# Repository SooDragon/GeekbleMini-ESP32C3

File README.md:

GeekbleMini-ESP32C3
=============
GeekbleMini-ESP32C3 문서에 오신것을 환영합니다

아두이노 IDE에서 쉽게 사용할 수 있는 Geekble Mini를 통해 WiFi, Bluetooth 기능을 여러분의 프로젝트에 구현할 수 있습니다

Geekble Mini 핀맵
-------------

GeekbleMini PinMap

Geekble Mini 회로도
-------------

GeekbleMini Schematic

Geekble Mini 치수도
-------------

GeekbleMini Dimension

Geekble Mini KiCad 라이브러리 by [@Alcyone-0022](https://github.com/Alcyone-0022)
-------------

KiCad 프로젝트에 사용 가능한 Footprint가 존재합니다.    
**Geekble Mini ESP32C3FH4.pretty** 폴더와 **Geekble Mini ESP32C3FH4.kicad_sym** 파일을 KiCad 프로젝트 폴더에 옮긴 뒤,    
각각 풋프린트 에디터→파일→라이브러리 추가→프로젝트 선택→확인→**Geekble Mini ESP32C3FH4.pretty** 폴더 선택,    
심볼 에디터→파일→라이브러리 추가→프로젝트 선택→확인→**Geekble Mini ESP32C3FH4.kicad_sym** 파일 선택하여 추가하신 뒤 사용해 주세요.

Geekble Mini Version Log
-------------
- Ver.1.0.0: 최초 공개 버전
- Ver.1.1.0: Vin/VUSB 설계 변경, VUSB에서 Vin 방향으로 전류가 흐르지 않도록 회로 및 아트웍 수정, Vin에 배터리가 연결 된 상태에서 USB를 연결할 수 있다
- Ver.1.1.1: 핀헤더에 의해 실크가 가려지지 않게 배치 수정
- Ver.2.0: A5(ADC1)핀 D5핀으로 재배치, 재배치에 따른 핀 위치 수정

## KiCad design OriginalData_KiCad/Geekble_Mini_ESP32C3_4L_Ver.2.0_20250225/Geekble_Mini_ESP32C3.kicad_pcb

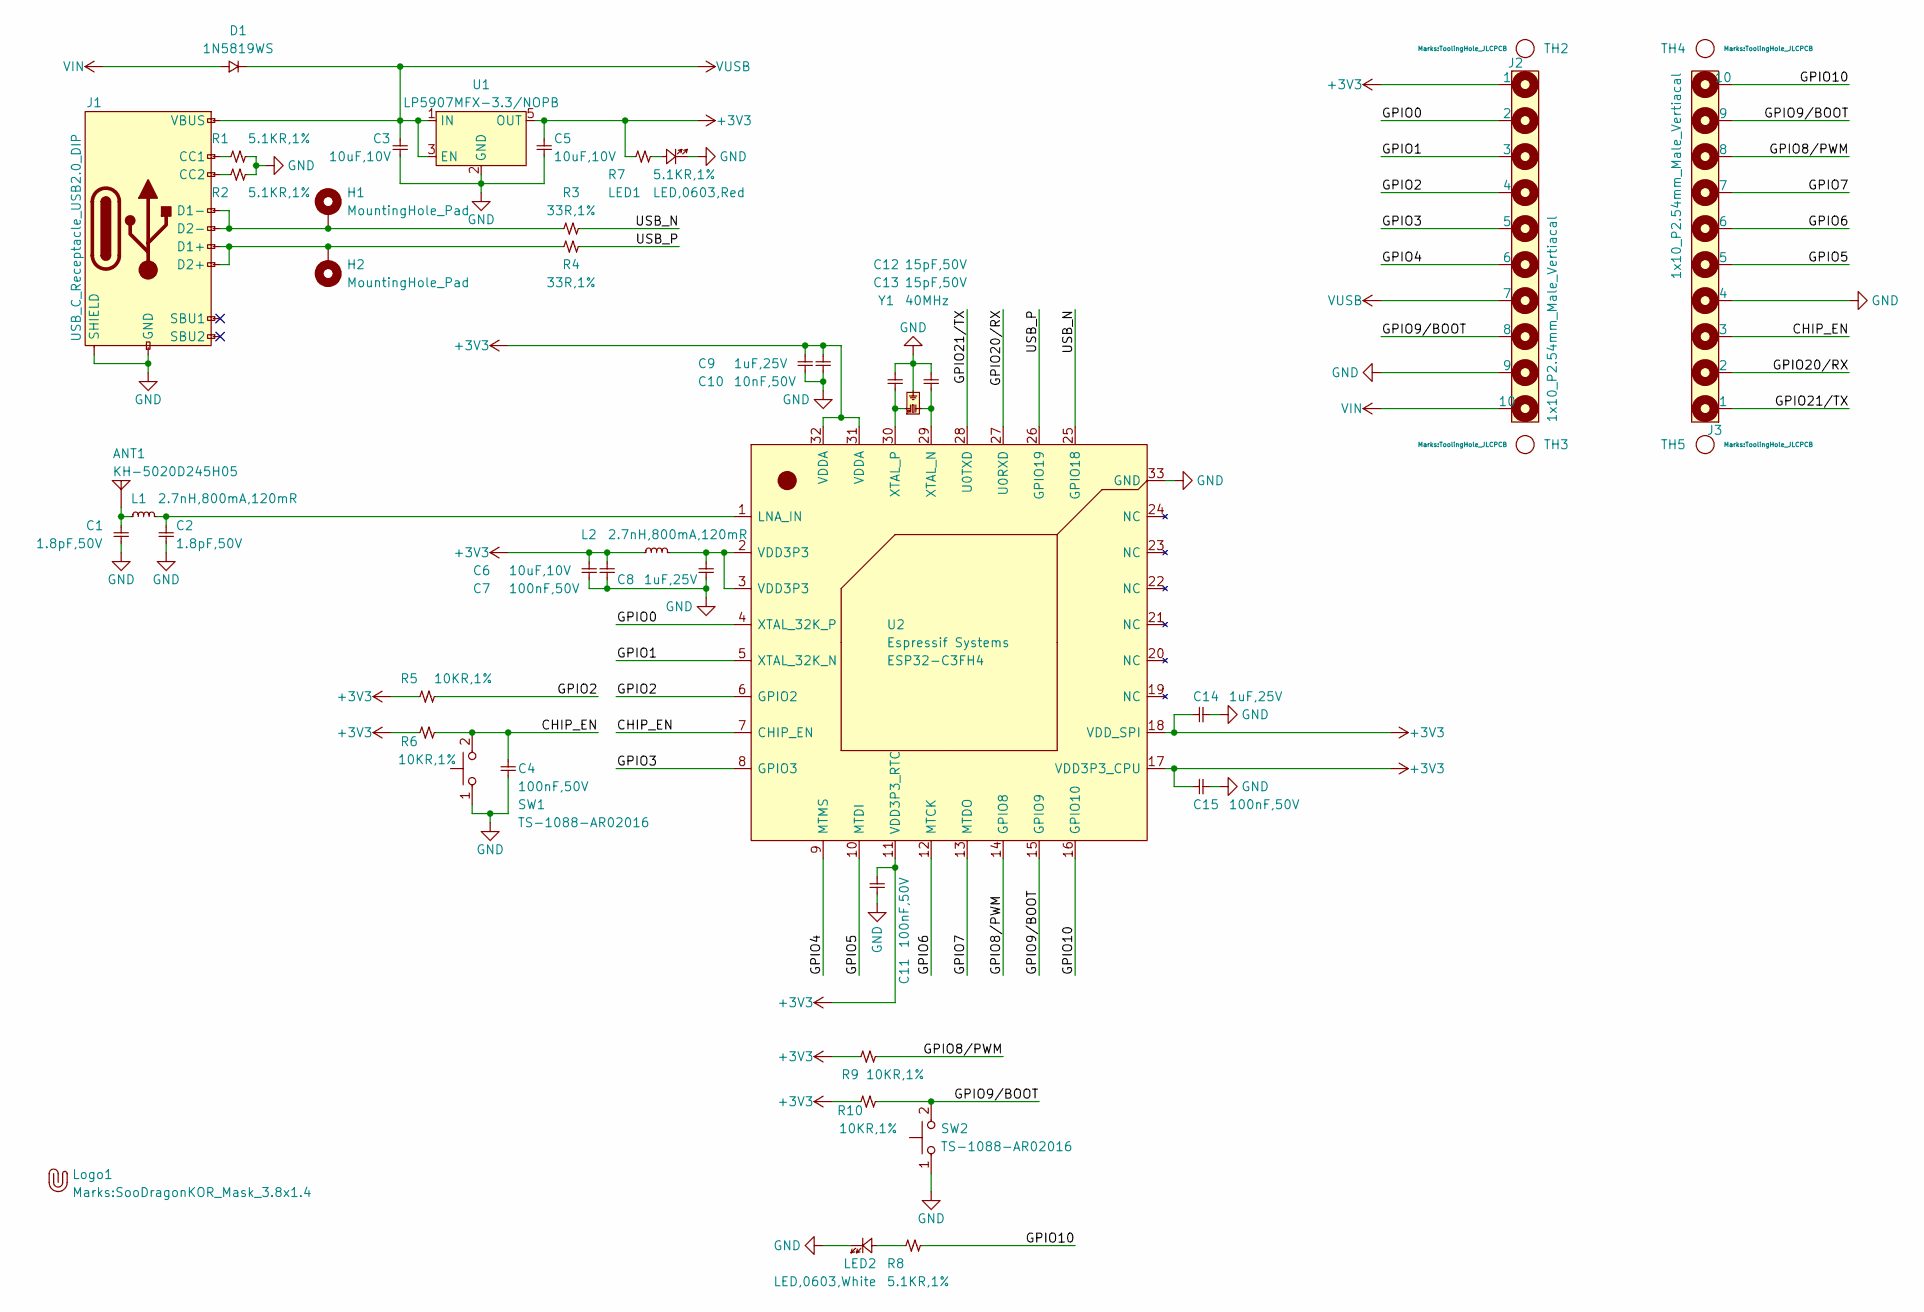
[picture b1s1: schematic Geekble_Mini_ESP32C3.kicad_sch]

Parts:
ANT1: KH-5020D245H05; ANT_5020; Manufacturer Part Number KH-5020D245H05; LCSC C45359218
C1, C2: 1.8pF,50V; C_0402; Manufacturer Part Number CC0402BRNPO9BN1R8; LCSC C327209
C3, C5, C6: 10uF,10V; C_0402; Manufacturer Part Number LDK105CBJ106MVLF; LCSC C386033
C4, C7, C11, C15: 100nF,50V; C_0402; Manufacturer Part Number CL05B104KB54PNC; LCSC C307331
C8, C9, C14: 1uF,25V; C_0402; Manufacturer Part Number CL05A105KA5NQNC; LCSC C52923
C10: 10nF,50V; C_0402; Manufacturer Part Number CL05B103KB5NNNC; LCSC C15195
C12, C13: 15pF,50V; C_0402; Manufacturer Part Number 0402CG150J500NT; LCSC C1548
D1: 1N5819WS; SOD-323F; Manufacturer Part Number 1N5819WS; LCSC C191023
H1, H2: MountingHole_Pad; 1x1_1.0piPad_SMD
J1: USB_C_Receptacle_USB2.0_DIP; USB_DIP,8.94x7.3mm; Manufacturer Part Number TYPE-C-31-M-12; LCSC C165948
J2, J3: 1x10_P2.54mm_Male_Vertiacal; 1x10_P2.54_CastellatedPad_PinHeader; Manufacturer Part Number 2541WV-10P; LCSC C5383117
L1, L2: 2.7nH,800mA,120mR; L_0402; Manufacturer Part Number LQG15HS2N7S02D; LCSC C77108
LED1: LED,0603,Red; LED_0603_Red; Manufacturer Part Number KT-0603R; LCSC C2286
LED2: LED,0603,White; LED_0603_White; LCSC C2290
Logo1: Geekble_Logo; SooDragonKOR_Mask_3.8x1.4
R1, R2, R7, R8: 5.1KR,1%; R_0402; Manufacturer Part Number 0402WGF5101TCE; LCSC C25905
R3, R4: 33R,1%; R_0402; Manufacturer Part Number 0402WGF330JTCE; LCSC C25105
R5, R6, R9, R10: 10KR,1%; R_0402; Manufacturer Part Number 0402WGF1002TCE; LCSC C25744
SW1, SW2: TS-1088-AR02016; TS-1088-AR020; Manufacturer Part Number TS-1088-AR02016; LCSC C720477
TH2, TH3, TH4, TH5: ToolingHole; ToolingHole_JLCPCB
U1: LP5907MFX-3.3/NOPB; SOT-23-5; Manufacturer Part Number LP5907MFX-3.3/NOPB; LCSC C80670
U2: ESP32-C3FH4; QFN-32-EP(5x5); Manufacturer Part Number ESP32-C3FH4; LCSC C2858491
Y1: 40MHz; SMD-3225_4P; Manufacturer Part Number X322540MPB4SI; LCSC C9010

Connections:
+3V3: C5.2, C6.2, C7.2, C9.2, C10.2, C11.2, C14.2, C15.2, J2.1, L2.1, R5.1, R6.1, R7.1, R9.1, R10.1, U1.5 (OUT), U2.11 (VDD3P3_RTC), U2.17 (VDD3P3_CPU), U2.18 (VDD_SPI), U2.31 (VDDA), U2.32 (VDDA)
/CHIP_EN: C4.2, J3.3, R6.2, SW1.2 (B), U2.7 (CHIP_EN)
/GPIO0: J2.2, U2.4 (XTAL_32K_P)
/GPIO1: J2.3, U2.5 (XTAL_32K_N)
/GPIO2: J2.4, R5.2, U2.6 (GPIO2)
/GPIO3: J2.5, U2.8 (GPIO3)
/GPIO4: J2.6, U2.9 (MTMS)
/GPIO5: J3.5, U2.10 (MTDI)
/GPIO6: J3.6, U2.12 (MTCK)
/GPIO7: J3.7, U2.13 (MTDO)
/GPIO8/PWM: J3.8, R9.2, U2.14 (GPIO8)
/GPIO9/BOOT: J2.8, J3.9, R10.2, SW2.2 (B), U2.15 (GPIO9)
/GPIO10: J3.10, R8.2, U2.16 (GPIO10)
/GPIO20/RX: J3.2, U2.27 (U0RXD)
/GPIO21/TX: J3.1, U2.28 (U0TXD)
/USB_N: R3.2, U2.25 (GPIO18)
/USB_P: R4.2, U2.26 (GPIO19)
GND: C1.1, C2.1, C3.1, C4.1, C5.1, C6.1, C7.1, C8.1, C9.1, C10.1, C11.1, C12.1, C13.1, C14.1, C15.1, J1.A1B12 (GND), J1.B1A12 (GND), J1.S1 (SHIELD), J1.S2 (SHIELD), J1.S3 (SHIELD), J1.S4 (SHIELD), J2.9, J3.4, LED1.C, LED2.C, R1.2, R2.2, SW1.1 (A), SW2.1 (A), U1.2 (GND), U2.33 (GND), Y1.2 (GND), Y1.4 (GND)
unnamed: ANT1.Feed, C1.2, L1.1
unnamed: C8.2, L2.2, U2.2 (VDD3P3), U2.3 (VDD3P3)
unnamed: J1.A5 (CC1), R1.1
unnamed: J1.B5 (CC2), R2.1
unnamed: H2.1, J1.A6 (D1+), J1.B6 (D2+), R4.1
unnamed: H1.1, J1.A7 (D1-), J1.B7 (D2-), R3.1
unnamed: LED1.A, R7.2
unnamed: LED2.A, R8.1
unnamed: C2.2, L1.2, U2.1 (LNA_IN)
unnamed: C13.2, U2.29 (XTAL_N), Y1.3 (OSC2)
unnamed: C12.2, U2.30 (XTAL_P), Y1.1 (OSC1)
VIN: D1.A, J2.10
VUSB: C3.2, D1.C, J1.A4B9 (VBUS), J1.B4A9 (VBUS), J2.7, U1.1 (IN), U1.3 (EN)

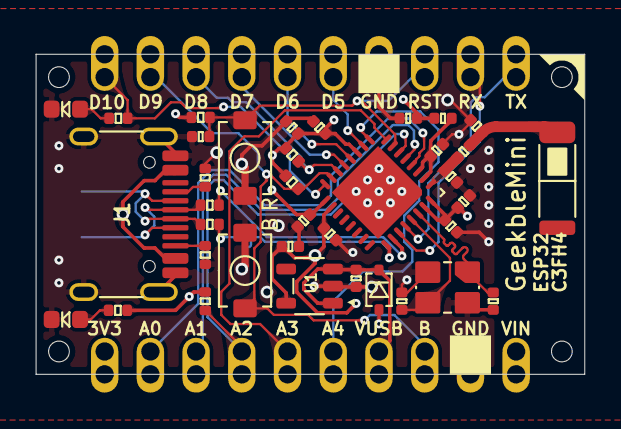
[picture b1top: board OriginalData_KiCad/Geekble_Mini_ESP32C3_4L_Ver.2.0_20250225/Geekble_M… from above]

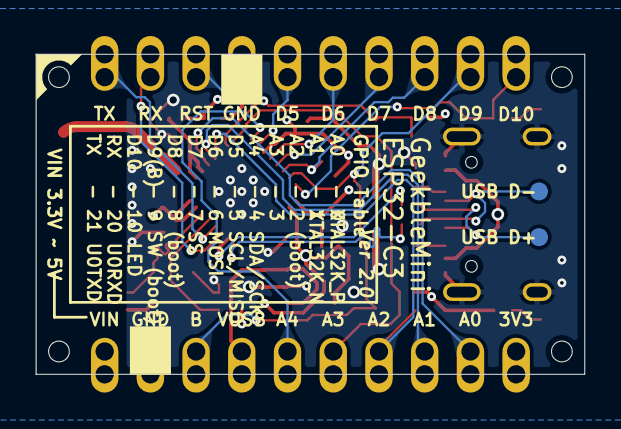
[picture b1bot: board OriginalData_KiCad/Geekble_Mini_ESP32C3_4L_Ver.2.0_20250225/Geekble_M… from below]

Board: 4 copper layers, 30.5 x 17.8 mm, 46 parts (4 on the bottom side), 31 nets.

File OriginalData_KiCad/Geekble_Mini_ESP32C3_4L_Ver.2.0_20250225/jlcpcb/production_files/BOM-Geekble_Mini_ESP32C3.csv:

Comment,Designator,Footprint,LCSC,Quantity
"10nF,50V",C10,C_0402,C15195,1
"15pF,50V","C12,C13",C_0402,C1548,2
USB_C_Receptacle_USB2.0_DIP,J1,"USB_DIP,8.94x7.3mm",C165948,1
1N5819WS,D1,SOD-323F,C191023,1
"LED,0603,Red",LED1,LED_0603_Red,C2286,1
"LED,0603,White",LED2,LED_0603_White,C2290,1
"33R,1%","R3,R4",R_0402,C25105,2
"10KR,1%","R10,R5,R6,R9",R_0402,C25744,4
"5.1KR,1%","R1,R2,R7,R8",R_0402,C25905,4
ESP32-C3FH4,U2,QFN-32-EP(5x5),C2858491,1
"100nF,50V","C11,C15,C4,C7",C_0402,C307331,4
"1.8pF,50V","C1,C2",C_0402,C327209,2
"10uF,10V","C3,C5,C6",C_0402,C386033,3
KH-5020D245H05,ANT1,ANT_5020,C45359218,1
"1uF,25V","C14,C8,C9",C_0402,C52923,3
1x10_P2.54mm_Male_Vertiacal,"J2,J3",1x10_P2.54_CastellatedPad_PinHeader,C5383117,2
TS-1088-AR02016,"SW1,SW2",TS-1088-AR020,C720477,2
"2.7nH,800mA,120mR","L1,L2",L_0402,C77108,2
LP5907MFX-3.3/NOPB,U1,SOT-23-5,C80670,1
40MHz,Y1,SMD-3225_4P,C9010,1
ToolingHole,TH4,ToolingHole_JLCPCB,,1
ToolingHole,TH5,ToolingHole_JLCPCB,,1
Geekble_Logo,Logo1,SooDragonKOR_Mask_3.8x1.4,,1
ToolingHole,TH3,ToolingHole_JLCPCB,,1
ToolingHole,TH2,ToolingHole_JLCPCB,,1
MountingHole_Pad,H2,1x1_1.0piPad_SMD,,1
MountingHole_Pad,H1,1x1_1.0piPad_SMD,,1

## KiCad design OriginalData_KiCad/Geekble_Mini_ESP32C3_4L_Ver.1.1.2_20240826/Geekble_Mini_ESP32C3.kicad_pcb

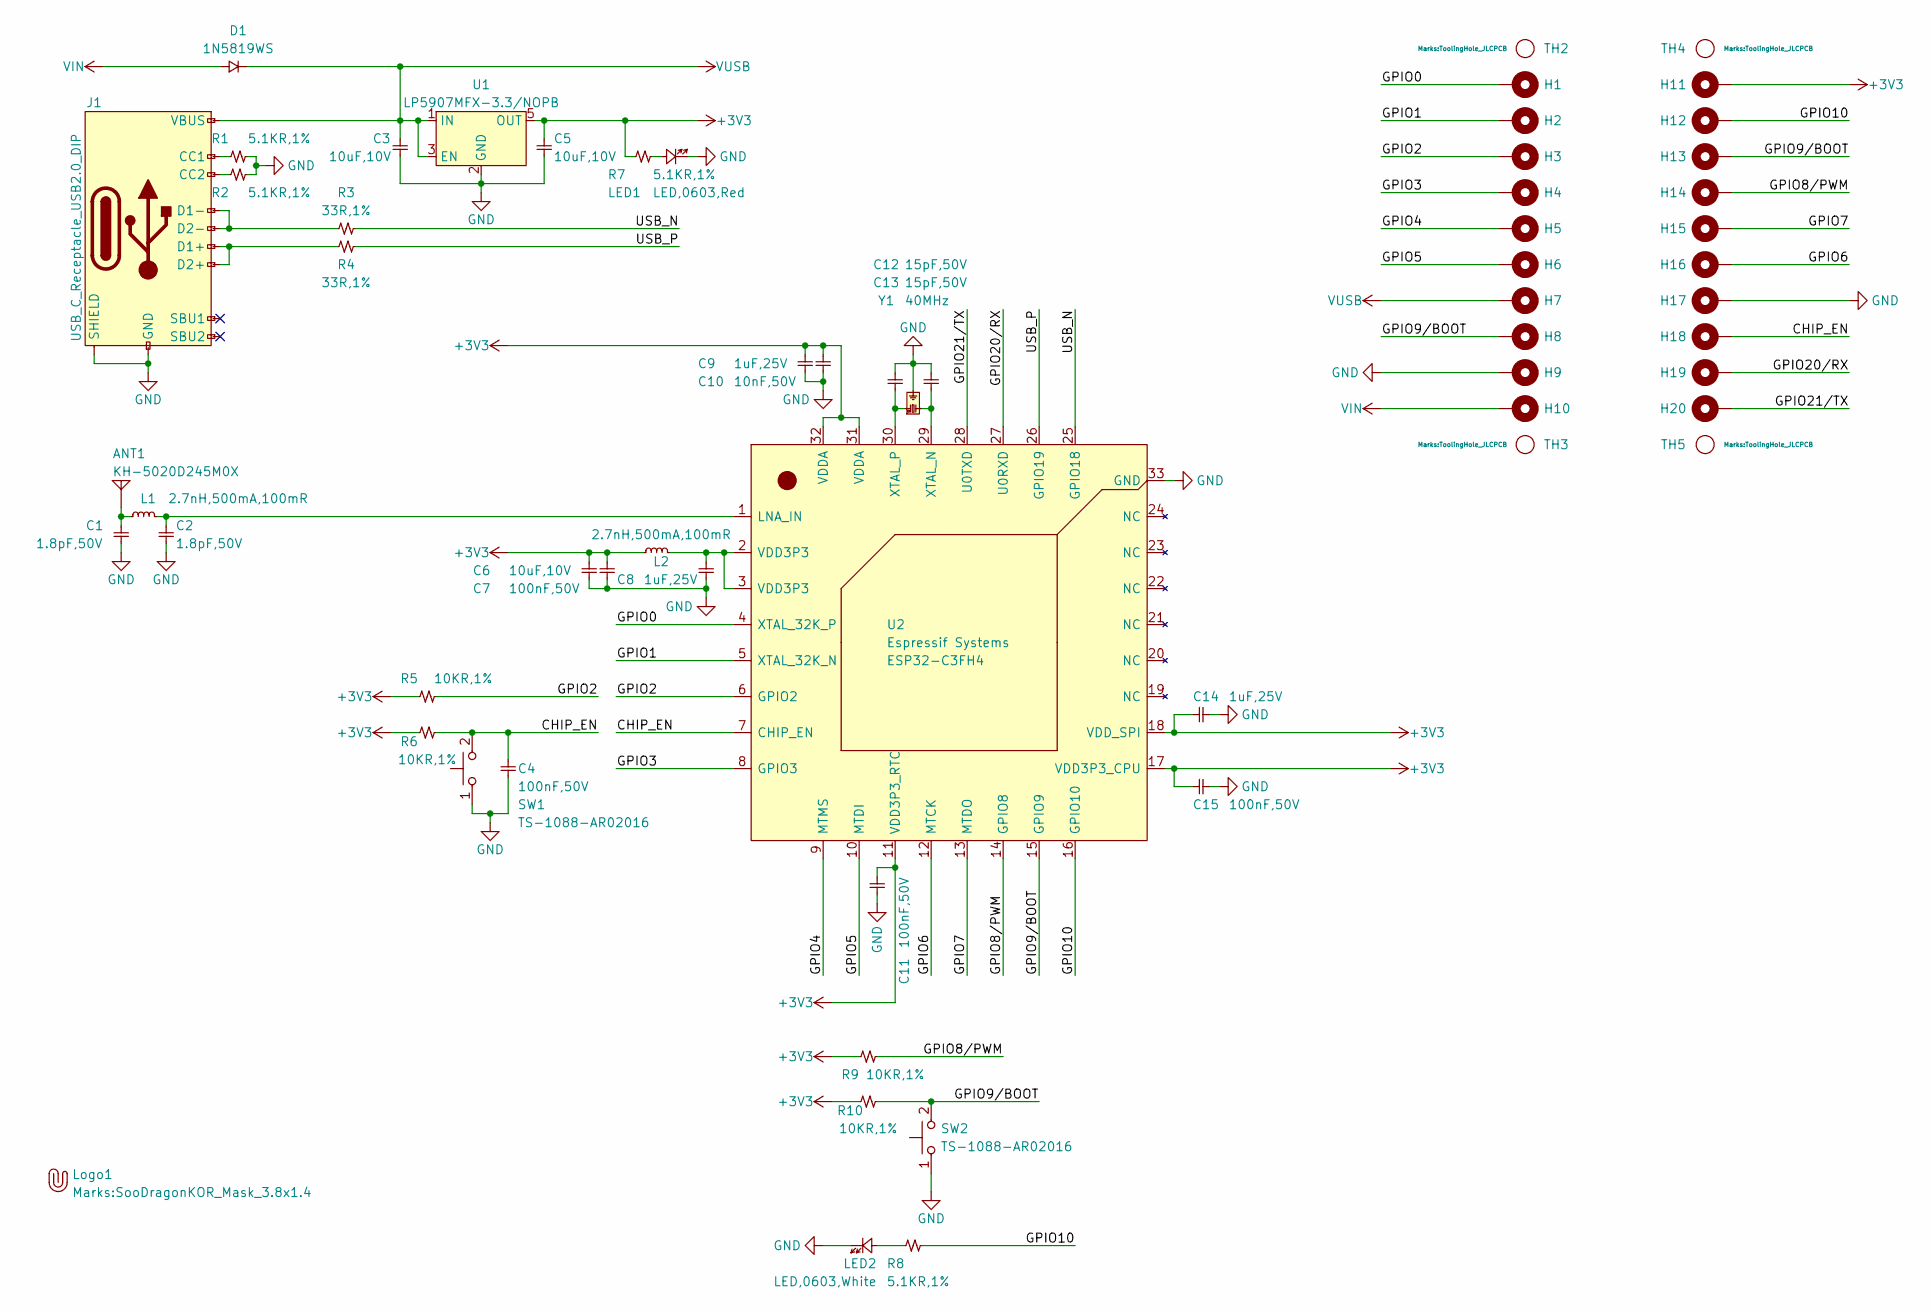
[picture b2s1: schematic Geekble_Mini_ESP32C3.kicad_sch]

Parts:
ANT1: KH-5020D245M0X; ANT_5020; Manufacturer Part Number KH-5020D245M0X; LCSC C454142
C1, C2: 1.8pF,50V; C_0402; Manufacturer Part Number CC0402BRNPO9BN1R8; LCSC C327209
C3, C5, C6: 10uF,10V; C_0402; Manufacturer Part Number LDK105CBJ106MVLF; LCSC C386033
C4, C7, C11, C15: 100nF,50V; C_0402; Manufacturer Part Number CL05B104KB54PNC; LCSC C307331
C8, C9, C14: 1uF,25V; C_0402; Manufacturer Part Number CL05A105KA5NQNC; LCSC C52923
C10: 10nF,50V; C_0402; Manufacturer Part Number CL05B103KB5NNNC; LCSC C15195
C12, C13: 15pF,50V; C_0402; Manufacturer Part Number 0402CG150J500NT; LCSC C1548
D1: 1N5819WS; SOD-323F; Manufacturer Part Number 1N5819WS; LCSC C191023
H1, H2, H3, H4, H5, H6, H7, H8, H9, H10, H11, H12, H13, H14, H15, H16, H17, H18, H19, H20: MountingHole_Pad; 1x1_P2.54_CastellatedPad
J1: USB_C_Receptacle_USB2.0_DIP; USB_DIP,8.94x7.3mm; Manufacturer Part Number TYPE-C-31-M-12; LCSC C165948
L1, L2: 2.7nH,500mA,100mR; L_0402; Manufacturer Part Number MLK1005S2N7ST000; LCSC C76791
LED1: LED,0603,Red; LED_0603_Red; Manufacturer Part Number KT-0603R; LCSC C2286
LED2: LED,0603,White; LED_0603_White; LCSC C2290
Logo1: Geekble_Logo; SooDragonKOR_Mask_3.8x1.4
R1, R2, R7, R8: 5.1KR,1%; R_0402; Manufacturer Part Number 0402WGF5101TCE; LCSC C25905
R3, R4: 33R,1%; R_0402; Manufacturer Part Number 0402WGF330JTCE; LCSC C25105
R5, R6, R9, R10: 10KR,1%; R_0402; Manufacturer Part Number 0402WGF1002TCE; LCSC C25744
SW1, SW2: TS-1088-AR02016; TS-1088-AR020; Manufacturer Part Number TS-1088-AR02016; LCSC C720477
TH2, TH3, TH4, TH5: ToolingHole; ToolingHole_JLCPCB
U1: LP5907MFX-3.3/NOPB; SOT-23-5; Manufacturer Part Number LP5907MFX-3.3/NOPB; LCSC C80670
U2: ESP32-C3FH4; QFN-32-EP(5x5); Manufacturer Part Number ESP32-C3FH4; LCSC C2858491
Y1: 40MHz; SMD-3225_4P; Manufacturer Part Number X322540MPB4SI; LCSC C9010

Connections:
+3V3: C5.2, C6.2, C7.2, C9.2, C10.2, C11.2, C14.2, C15.2, H11.1, L2.1, R5.1, R6.1, R7.1, R9.1, R10.1, U1.5 (OUT), U2.11 (VDD3P3_RTC), U2.17 (VDD3P3_CPU), U2.18 (VDD_SPI), U2.31 (VDDA), U2.32 (VDDA)
/CHIP_EN: C4.2, H18.1, R6.2, SW1.2 (B), U2.7 (CHIP_EN)
/GPIO0: H1.1, U2.4 (XTAL_32K_P)
/GPIO1: H2.1, U2.5 (XTAL_32K_N)
/GPIO2: H3.1, R5.2, U2.6 (GPIO2)
/GPIO3: H4.1, U2.8 (GPIO3)
/GPIO4: H5.1, U2.9 (MTMS)
/GPIO5: H6.1, U2.10 (MTDI)
/GPIO6: H16.1, U2.12 (MTCK)
/GPIO7: H15.1, U2.13 (MTDO)
/GPIO8/PWM: H14.1, R9.2, U2.14 (GPIO8)
/GPIO9/BOOT: H8.1, H13.1, R10.2, SW2.2 (B), U2.15 (GPIO9)
/GPIO10: H12.1, R8.2, U2.16 (GPIO10)
/GPIO20/RX: H19.1, U2.27 (U0RXD)
/GPIO21/TX: H20.1, U2.28 (U0TXD)
/USB_N: R3.2, U2.25 (GPIO18)
/USB_P: R4.2, U2.26 (GPIO19)
GND: C1.1, C2.1, C3.1, C4.1, C5.1, C6.1, C7.1, C8.1, C9.1, C10.1, C11.1, C12.1, C13.1, C14.1, C15.1, H9.1, H17.1, J1.A1B12 (GND), J1.B1A12 (GND), J1.S1 (SHIELD), J1.S2 (SHIELD), J1.S3 (SHIELD), J1.S4 (SHIELD), LED1.C, LED2.C, R1.2, R2.2, SW1.1 (A), SW2.1 (A), U1.2 (GND), U2.33 (GND), Y1.2 (GND), Y1.4 (GND)
unnamed: ANT1.Feed, C1.2, L1.1
unnamed: C8.2, L2.2, U2.2 (VDD3P3), U2.3 (VDD3P3)
unnamed: J1.A5 (CC1), R1.1
unnamed: J1.B5 (CC2), R2.1
unnamed: J1.A6 (D1+), J1.B6 (D2+), R4.1
unnamed: J1.A7 (D1-), J1.B7 (D2-), R3.1
unnamed: LED1.A, R7.2
unnamed: LED2.A, R8.1
unnamed: C2.2, L1.2, U2.1 (LNA_IN)
unnamed: C13.2, U2.29 (XTAL_N), Y1.3 (OSC2)
unnamed: C12.2, U2.30 (XTAL_P), Y1.1 (OSC1)
VIN: D1.A, H10.1
VUSB: C3.2, D1.C, H7.1, J1.A4B9 (VBUS), J1.B4A9 (VBUS), U1.1 (IN), U1.3 (EN)

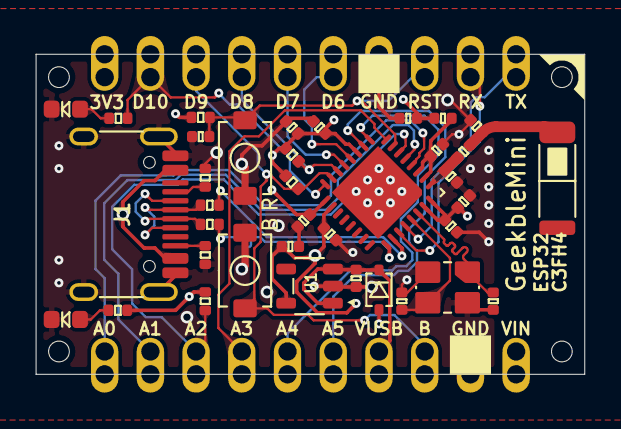
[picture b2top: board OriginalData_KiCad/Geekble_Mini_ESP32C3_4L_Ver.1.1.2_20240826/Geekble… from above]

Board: 4 copper layers, 30.5 x 17.8 mm, 62 parts (0 on the bottom side), 31 nets.

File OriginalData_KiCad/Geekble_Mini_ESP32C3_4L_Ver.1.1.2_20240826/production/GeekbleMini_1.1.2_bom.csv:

Designator,Footprint,Quantity,Value,LCSC Part #
ANT1,ANT_5020,1,KH-5020D245M0X,C454142
"C1, C2",C_0402,2,"1.8pF,50V",C327209
C10,C_0402,1,"10nF,50V",C15195
"C11, C15, C4, C7",C_0402,4,"100nF,50V",C307331
"C12, C13",C_0402,2,"15pF,50V",C1548
"C14, C8, C9",C_0402,3,"1uF,25V",C52923
"C3, C5, C6",C_0402,3,"10uF,10V",C386033
D1,SOD-323F,1,1N5819WS,C191023
J1,"USB_DIP,8.94x7.3mm",1,USB_C_Receptacle_USB2.0_DIP,C165948
"L1, L2",L_0402,2,"2.7nH,500mA,100mR",C76791
LED1,LED_0603_Red,1,"LED,0603,Red",C2286
LED2,LED_0603_White,1,"LED,0603,White",C2290
"R1, R2, R7, R8",R_0402,4,"5.1KR,1%",C25905
"R10, R5, R6, R9",R_0402,4,"10KR,1%",C25744
"R3, R4",R_0402,2,"33R,1%",C25105
"SW1, SW2",TS-1088-AR020,2,TS-1088-AR02016,C720477
U1,SOT-23-5,1,LP5907MFX-3.3/NOPB,C80670
U2,QFN-32-EP(5x5),1,ESP32-C3FH4,C2858491
Y1,SMD-3225_4P,1,40MHz,C9010

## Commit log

2024-06-04 DataUpload
    DataUpload
2024-06-07 Image Update
    Image Update
2024-09-14 pinmap update
    pinmap update
2024-09-14 delate old version pinmap
2024-09-26 1.1.2 update
    1.1.2 update
2025-02-26 Update2.0
2025-02-26 STEP
2025-02-27 2.0 diagram
2025-02-27 V2 Diagram
2025-02-27 PICV2
2025-02-27 V2 SCH
2025-03-11 add geekblemini kicad lib
2025-03-11 add symbol img
2025-03-11 modify 3d model path
2025-07-02 ud
    ud
